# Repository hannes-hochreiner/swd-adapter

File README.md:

# SWD-Adapter

This is an adapter board for a five-pin SWD connector I used in some of my projects.

**Note:** The board is designed for 0.8 mm PCBs.
1.6 mm PCBs, as are common with many PCB manufacturers will not work.

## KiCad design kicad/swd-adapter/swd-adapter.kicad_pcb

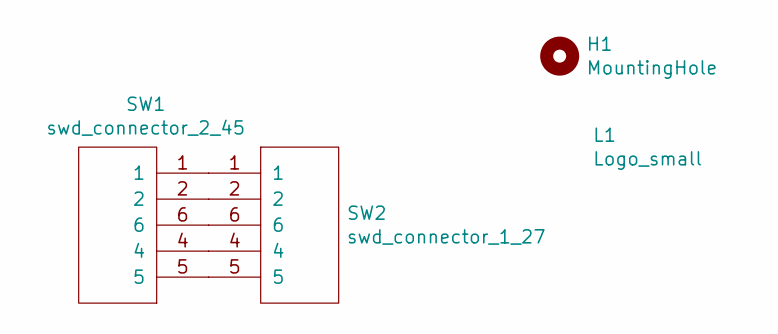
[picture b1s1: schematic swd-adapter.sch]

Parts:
H1: MountingHole; MountingHole_2.2mm_M2_Pad_Via
L1: Logo_small; logo_small
SW1: swd_connector_2_45; swd_connector_2_54; Manufacturer Part Number M20-8760342; Digi-Key Part Number 952-1922-ND
SW2: swd_connector_1_27; Manufacturer Part Number GRPB032VWVN-RC; Digi-Key Part Number S9015E-03-ND

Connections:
unnamed: SW1.1, SW2.1
unnamed: SW1.2, SW2.2
unnamed: SW1.4, SW2.4
unnamed: SW1.5, SW2.5
unnamed: SW1.6, SW2.6

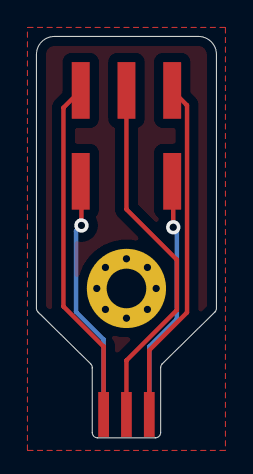
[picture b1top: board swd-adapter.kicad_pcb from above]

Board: 2 copper layers, 10.0 x 22.3 mm, 4 parts (1 on the bottom side), 5 nets.

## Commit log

2021-06-04 added pour
2021-06-05 add boxes
2021-07-11 add picture
2021-07-11 fix image syntax
